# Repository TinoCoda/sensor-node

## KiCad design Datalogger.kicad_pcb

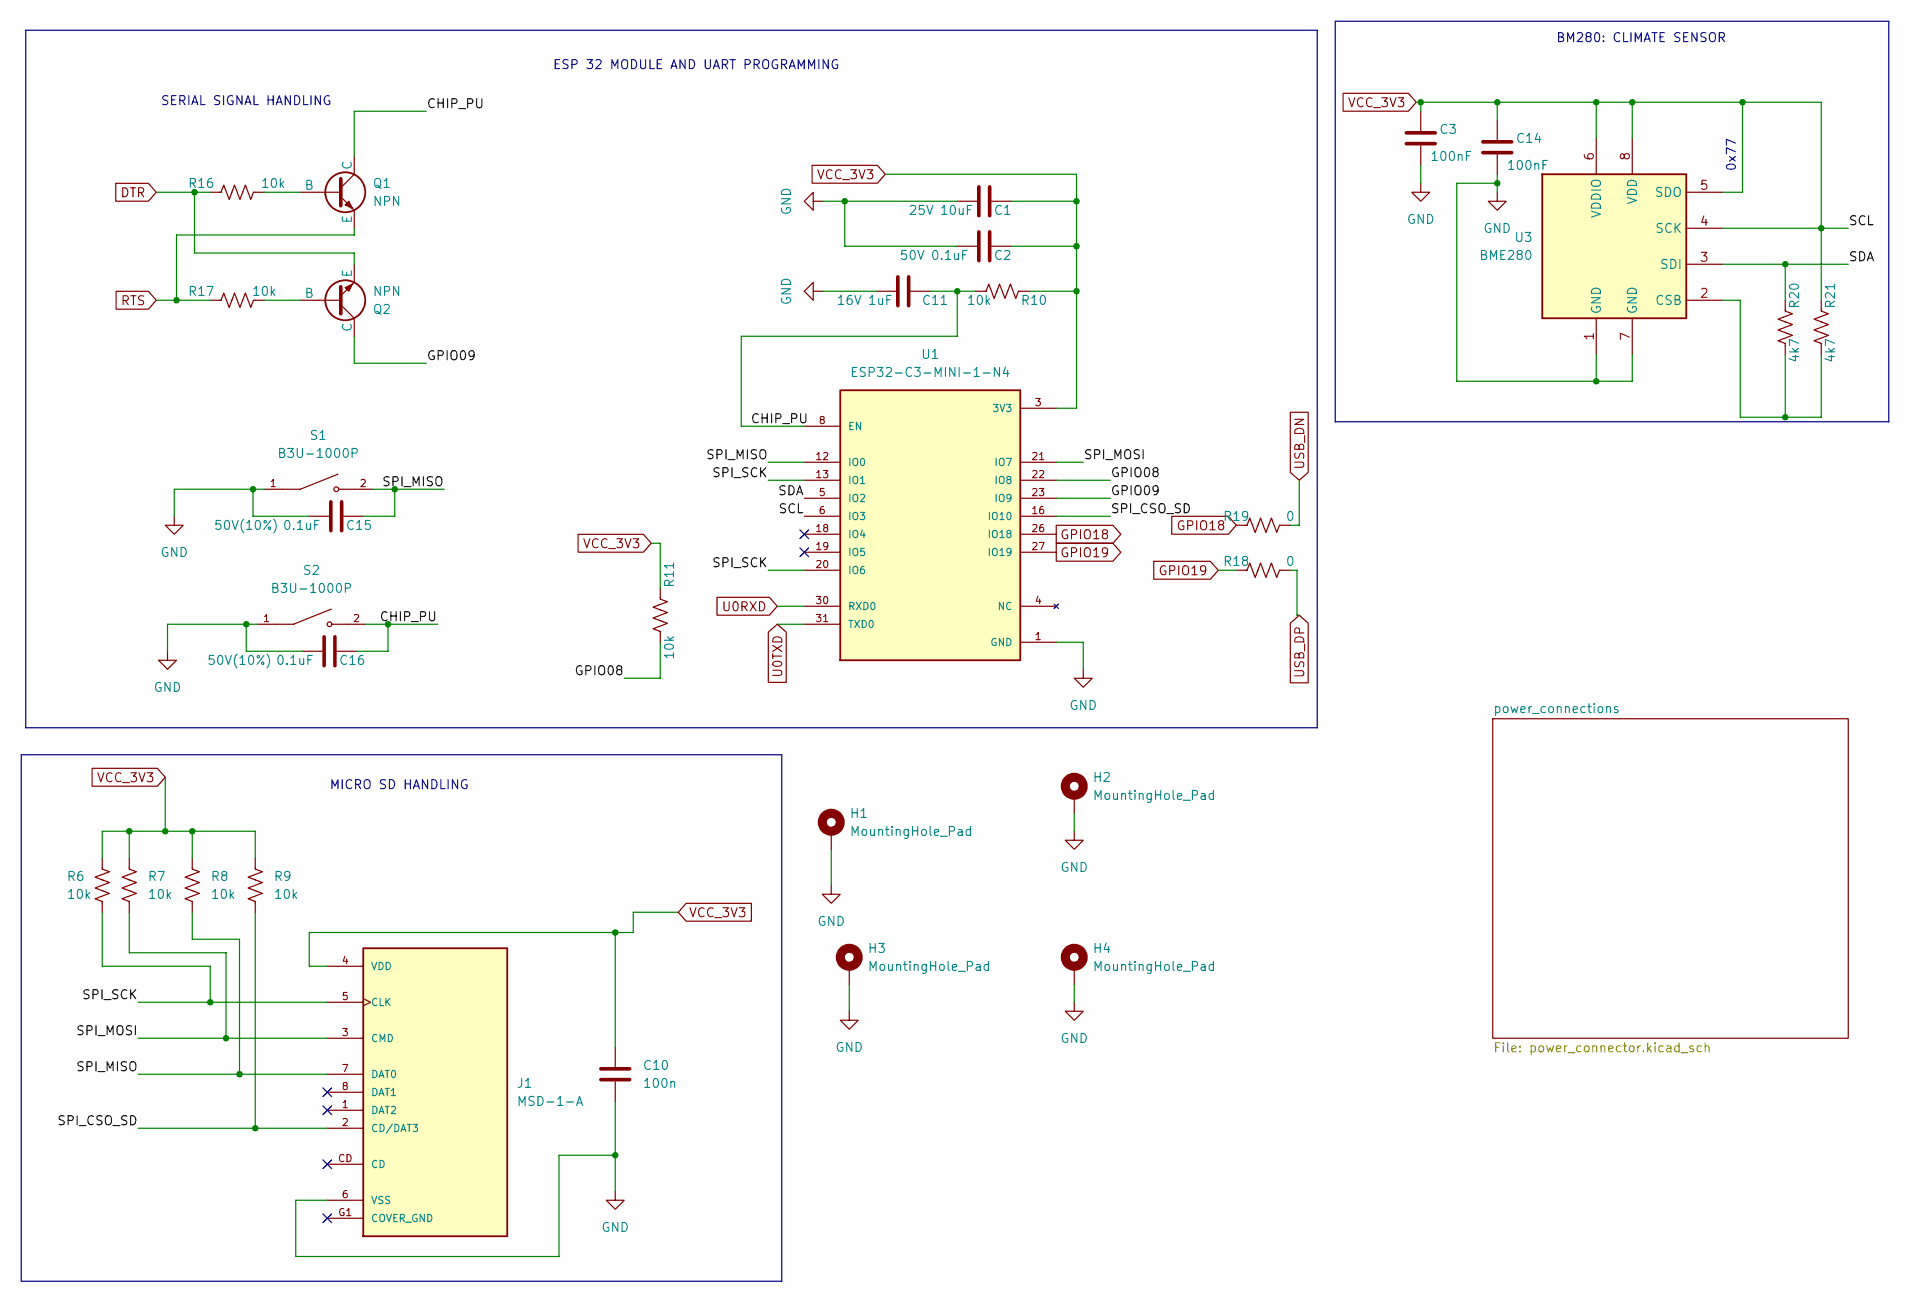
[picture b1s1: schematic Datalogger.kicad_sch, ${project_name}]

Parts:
C1: 10uF; C_0603_1608Metric
C2, C15, C16: 0.1uF; C_0402_1005Metric
C3, C14: 100nF; C_01005_0402Metric
C10: 100n; C_0402_1005Metric
C11: 1uF; C_0201_0603Metric
H1, H2, H3, H4: MountingHole_Pad; MountingHole_2.2mm_M2_DIN965_Pad
J1: MSD-1-A; CUI_MSD-1-A; PARTREV 1.0
Q1, Q2: NPN; SOT-23-3
R6, R7, R8, R9, R10, R11, R16, R17: 10k; R_0402_1005Metric
R18, R19: 0; R_0402_1005Metric
R20, R21: 4k7; R_0402_1005Metric
S1, S2: B3U-1000P; SW_B3U-1000P
U1: ESP32-C3-MINI-1-N4; XCVR_ESP32-C3-MINI-1-N4; PARTREV v1.0
U3: BME280; Bosch_LGA-8_2.5x2.5mm_P0.65mm_ClockwisePinNumbering

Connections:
/CHIP_PU: C11.1, C16.1, Q1.1 (C), R10.2, S2.2, U1.8 (EN)
/GPIO08: R11.2, U1.22 (IO8)
/GPIO09: Q2.1 (C), U1.23 (IO9)
/SDA: R20.1, U1.5 (IO2), U3.3 (SDI)
/SPI_CSO_SD: J1.2 (CD/DAT3), R9.2, U1.16 (IO10)
/SPI_MISO: C15.1, J1.7 (DAT0), R8.2, S1.2, U1.12 (IO0)
/SPI_MOSI: J1.3 (CMD), R7.2, U1.21 (IO7)
/SPI_SCK: J1.5 (CLK), R6.2, U1.13 (IO1), U1.20 (IO6)
DTR: Q2.3 (E), R16.1; also elsewhere on the board
GND: C1.2, C2.2, C3.2, C10.2, C11.2, C14.2, C15.2, C16.2, H1.1, H2.1, H3.1, H4.1, J1.6 (VSS), S1.1, S2.1, U1.1 (GND), U1.2 (GND), U1.11 (GND), U1.14 (GND), U1.36 (GND), U1.37 (GND), U1.38 (GND), U1.39 (GND), U1.40 (GND), U1.41 (GND), U1.42 (GND), U1.43 (GND), U1.44 (GND), U1.45 (GND), U1.46 (GND), U1.47 (GND), U1.48 (GND), U1.49_1 (GND), U1.49_2 (GND), U1.49_3 (GND), U1.49_4 (GND), U1.49_5 (GND), U1.49_6 (GND), U1.49_7 (GND), U1.49_8 (GND), U1.49_9 (GND), U1.50 (GND), U1.51 (GND), U1.52 (GND), U1.53 (GND), U3.1 (GND), U3.7 (GND); also elsewhere on the board
GPIO18: R19.1, U1.26 (IO18); also elsewhere on the board
GPIO19: R18.1, U1.27 (IO19); also elsewhere on the board
unnamed: Q1.2 (B), R16.2
unnamed: Q2.2 (B), R17.2
unnamed: R20.2, R21.2, U3.2 (CSB)
RTS: Q1.3 (E), R17.1; also elsewhere on the board
U0RXD: U1.30 (RXD0); also elsewhere on the board
U0TXD: U1.31 (TXD0); also elsewhere on the board
USB_DN: R19.2; also elsewhere on the board
USB_DP: R18.2; also elsewhere on the board
VCC_3V3: C1.1, C2.1, C3.1, C10.1, C14.1, J1.4 (VDD), R6.1, R7.1, R8.1, R9.1, R10.1, R11.1, R21.1, U1.3 (3V3), U1.6 (IO3), U3.4 (SCK), U3.5 (SDO), U3.6 (VDDIO), U3.8 (VDD); also elsewhere on the board

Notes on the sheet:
0x77
ESP 32 MODULE AND UART PROGRAMMING
MICRO SD HANDLING
BM280: CLIMATE SENSOR
SERIAL SIGNAL HANDLING

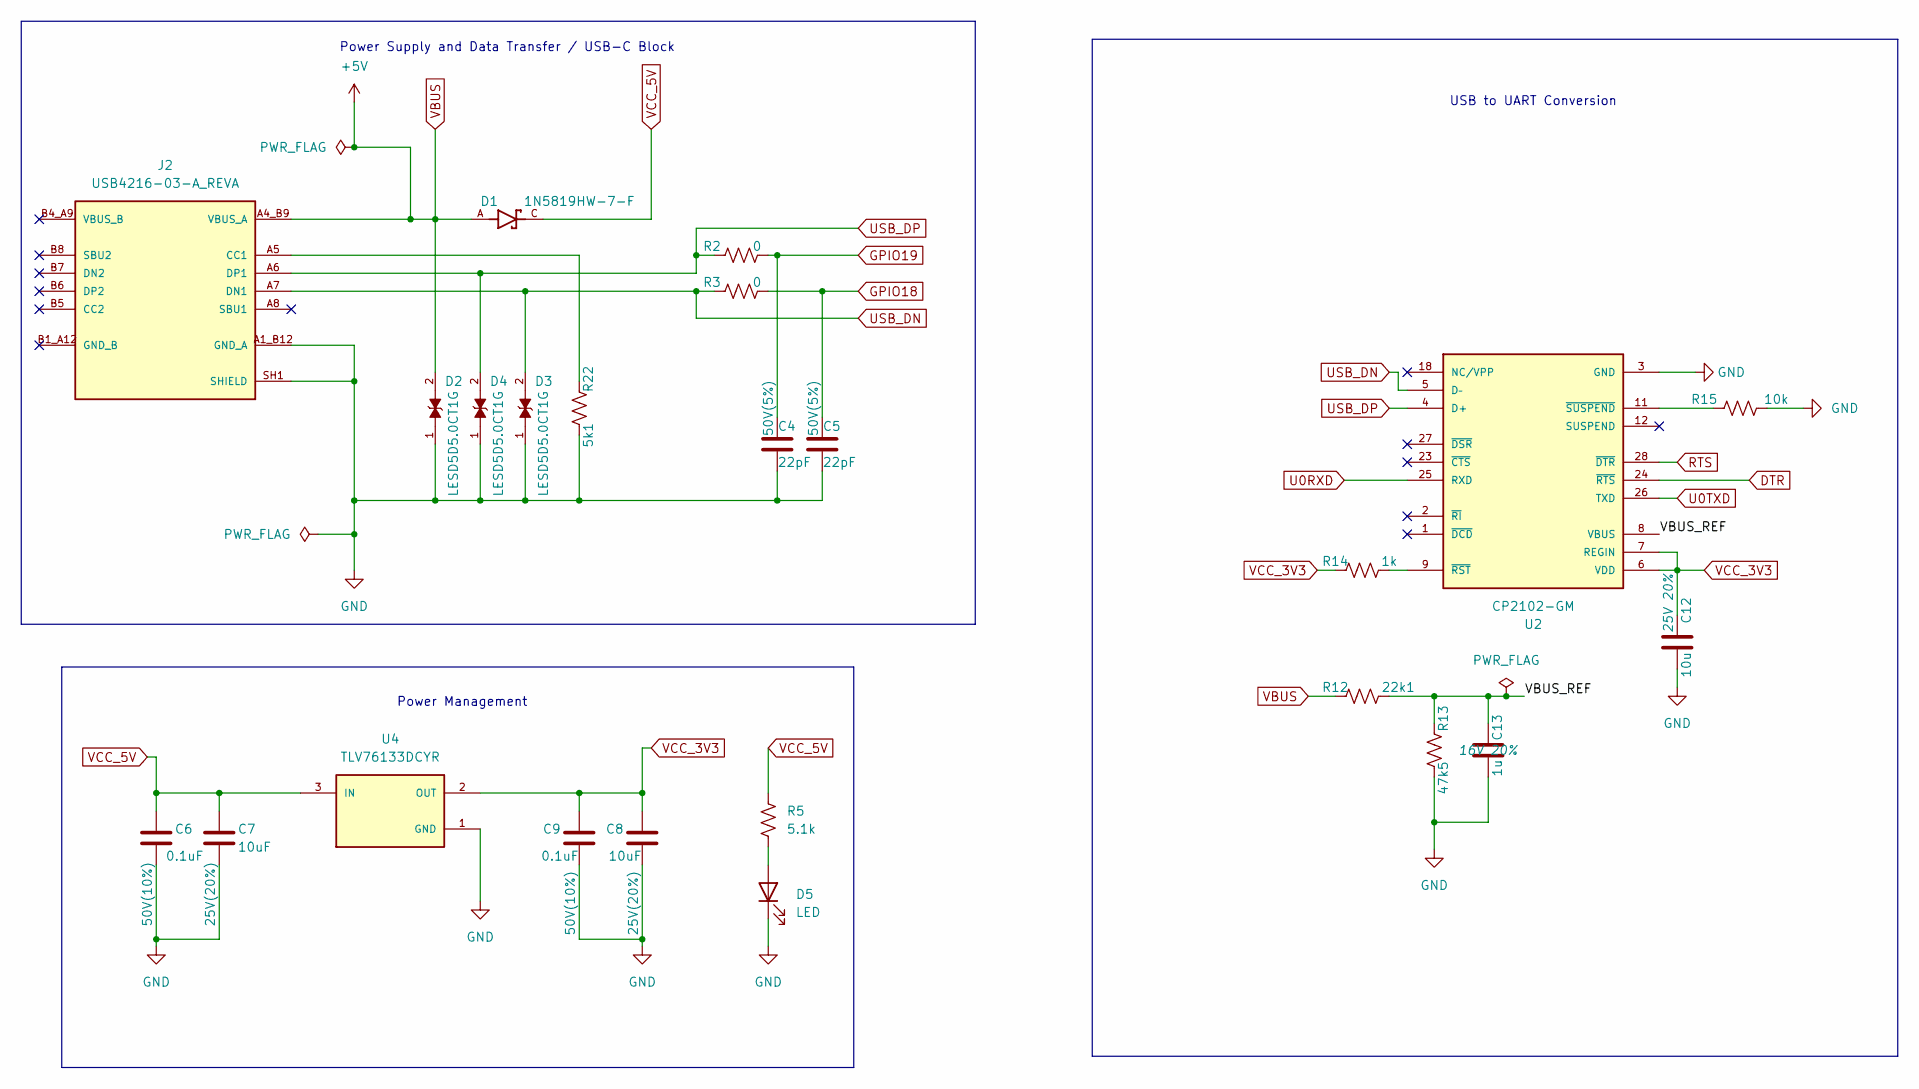
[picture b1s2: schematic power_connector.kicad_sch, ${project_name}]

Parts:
C4, C5: 22pF; C_01005_0402Metric
C6, C9: 0.1uF; C_0402_1005Metric
C7, C8: 10uF; C_0603_1608Metric
C12: 10u; C_0603_1608Metric
C13: 1u; C_0201_0603Metric
D1: 1N5819HW-7-F; SOD3715X145N; PARTREV 18-2; DigiKey_Part_Number 1N5819HW-FDICT-ND
D2, D3, D4: LESD5D5.0CT1G; TVS_LESD5D5.0CT1G; PARTREV O
D5: LED; LED_0402_1005Metric
J2: USB4216-03-A_REVA; GCT_USB4216-03-A_REVA; PARTREV A
R2, R3: 0; R_0402_1005Metric
R5: 5.1k; R_0402_1005Metric
R12: 22k1; R_0402_1005Metric
R13: 47k5; R_0402_1005Metric
R14: 1k; R_0402_1005Metric
R15: 10k; R_0402_1005Metric
R22: 5k1; R_0402_1005Metric
U2: CP2102-GM; QFN50P500X500X100-29N; PARTREV 1.8
U4: TLV76133DCYR; VREG_TLV76133DCYR; PARTREV B

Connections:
/power_connections/VBUS_REF: C13.1, R12.1, R13.1, U2.8 (VBUS)
DTR: U2.24 (~RTS); also elsewhere on the board
GND: C4.2, C5.2, C6.2, C7.2, C8.2, C9.2, C12.2, C13.2, D2.1, D3.1, D4.1, D5.1 (K), J2.A1_B12 (GND_A), J2.SH1 (SHIELD), J2.SH2 (SHIELD), J2.SH3 (SHIELD), J2.SH4 (SHIELD), R13.2, R15.2, R22.2, U2.3 (GND), U2.29 (GND), U4.1 (GND); also elsewhere on the board
GPIO18: C5.1, R3.2; also elsewhere on the board
GPIO19: C4.1, R2.2; also elsewhere on the board
unnamed: D5.2 (A), R5.2
unnamed: J2.A5 (CC1), R22.1
unnamed: R14.1, U2.9 (~RST)
unnamed: R15.1, U2.11 (~SUSPEND)
RTS: U2.28 (~DTR); also elsewhere on the board
U0RXD: U2.25 (RXD); also elsewhere on the board
U0TXD: U2.26 (TXD); also elsewhere on the board
USB_DN: D3.2, J2.A7 (DN1), R3.1, U2.5 (D–); also elsewhere on the board
USB_DP: D4.2, J2.A6 (DP1), R2.1, U2.4 (D+); also elsewhere on the board
VBUS: D1.A, D2.2, J2.A4_B9 (VBUS_A), R12.2
VCC_3V3: C8.1, C9.1, C12.1, R14.2, U2.6 (VDD), U2.7 (REGIN), U4.2 (OUT), U4.4 (OUT); also elsewhere on the board
VCC_5V: C6.1, C7.1, D1.C, R5.1, U4.3 (IN)

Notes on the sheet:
USB to UART Conversion
Power Supply and Data Transfer / USB-C Block
Power Management

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
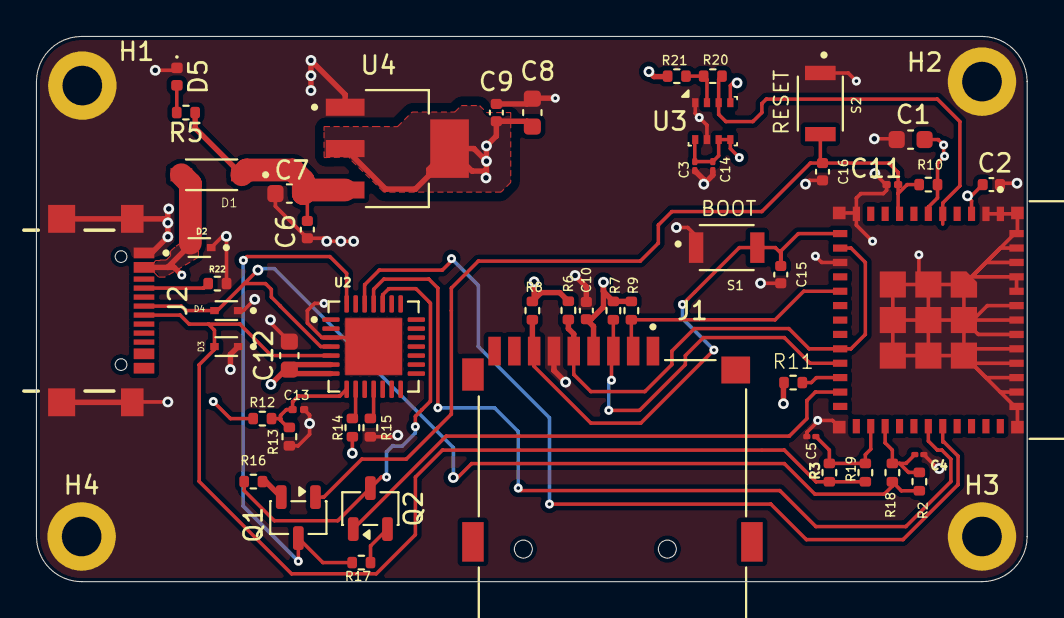
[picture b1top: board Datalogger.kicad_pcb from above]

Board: 4 copper layers, 55.0 x 30.3 mm, 55 parts (0 on the bottom side), 28 nets.

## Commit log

2025-12-14 first design - 4 layer board
2025-12-31 finished 4 layer board
2026-01-03 add docs, symbols and prints
